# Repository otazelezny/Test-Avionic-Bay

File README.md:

# Test-Avionic-Bay
Avionic bay for testing purposes.

just an general idea how it should looks

v2 (7/31/2024)

schematic v1

schematic partly routed

V1.2 - To improve
    -   Better routing 
    -   coil - XFL4020-152ML                    DONE
    -   more troughput trough routes
    -   probe pins 
    -   more outputs and systematic desing
    -   40x40 hole pattern
    -   more cabel holes
    -   big ground plane to sheelding
    -   external 5v input for easier control
    -   continuity charge sense
    -   4 pyro channels                         DONE
    -   second IC for redandency
    -   micro-sd
    -   Thermistor 100k
    -   Neopixel output

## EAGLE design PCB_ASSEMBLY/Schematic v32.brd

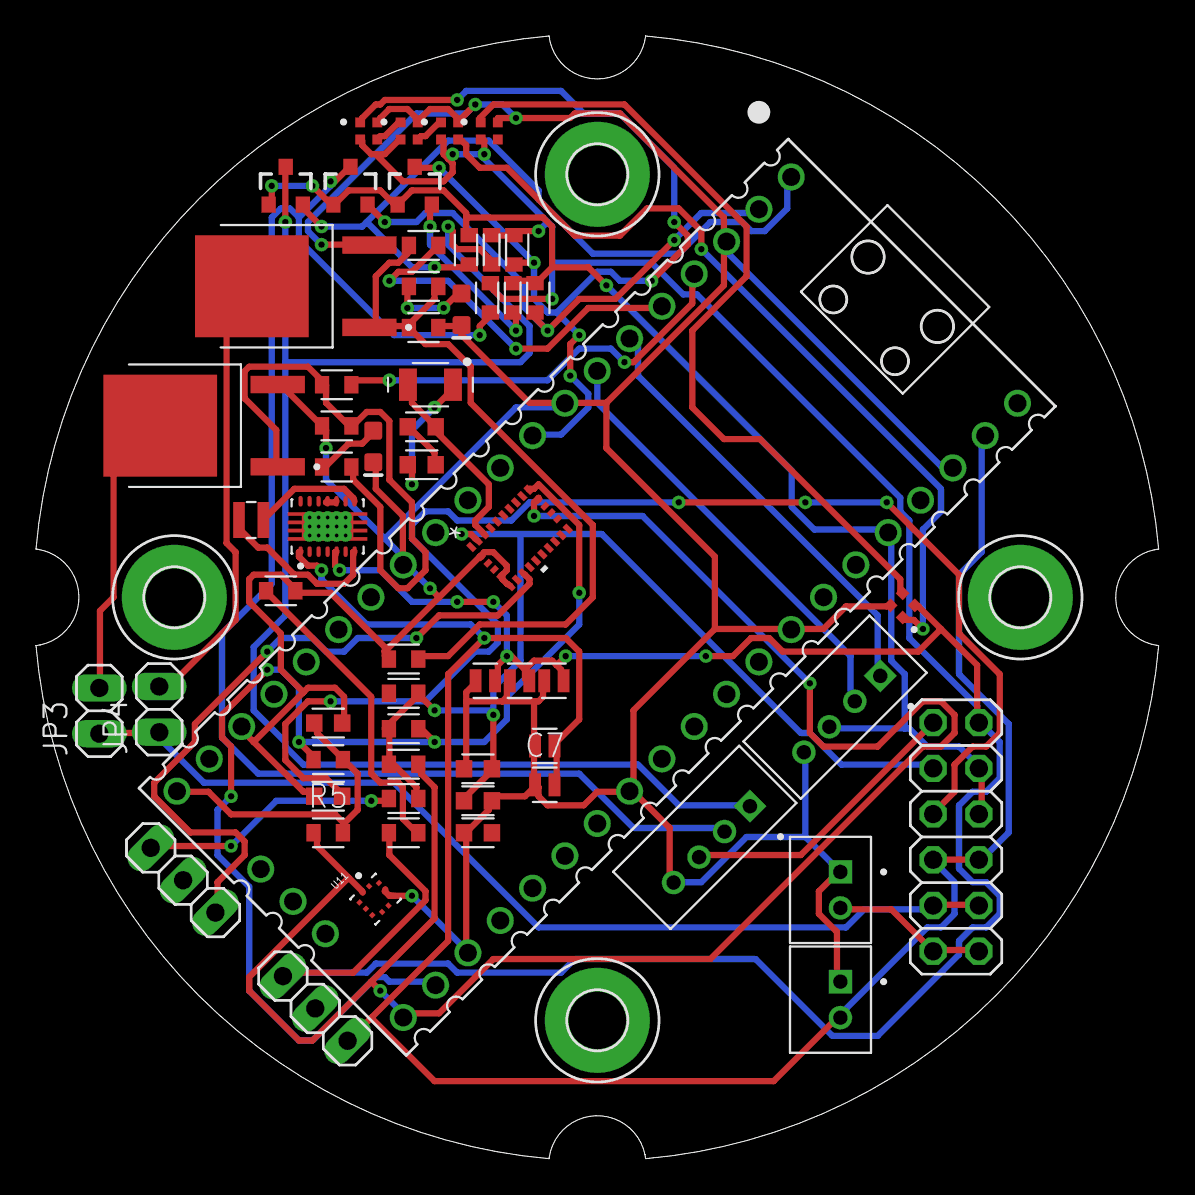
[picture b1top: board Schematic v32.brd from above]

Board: 4 copper layers, 62.2 x 62.2 mm, 64 parts (0 on the bottom side), 45 nets.

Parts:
C1: 1μF; CAPC1608X85
C2, C4, C5: 100nF; CAPC1608X85
C3, C11, C12: 120nF; CAPC1608X85
C6: 10n; CAPC1110X102
C7: 100n; CAPC1110X102
C8, C10: 22UF; CAPC1110X102
C9: 22uF; CAPC1110X102
D1, D2: Red; LED-0603
H1, H2, H3, H4: MOUNT-PAD-ROUND3.2; 3,2-PAD
J1, J2: B4B-PH-KL(LF)(SN); JST_B4B-PH-KL(LF)(SN)
J3, J4: B2B-PH-K-S(LF)(SN); JST_B2B-PH-K-S(LF)(SN)
JP1, JP2: PINHD-1X3; 1X03
JP3, JP4: PINHD-1X2; 1X02
JP5: PINHD-2X6; 2X06
L1: 1.5uH; INDUCTOR_2X2
Q1, Q2, Q3: 220mA/50V/3.5Ω; SOT23-3
Q4, Q5: AOD4184A; DPAK228P994X240-4N
R1, R4, R7, R8, R9, R10, R11, R12: 10K; RESC1608X60
R2, R3, R5, R6: 4.7K; RESC1608X60
R13, R14, R15, R16, R17, R18, R19, R20, R21: RESC1608X60
U1: BNO055QFN_BNO055_BOS; QFN_BNO055_BOS
U2: RASPBERRY_PICOTH; PICO-PKG-TH
U3, U4, U5, U6, U7: 4492; LED_4492
U8: TPS63020DSJR; IC_TPS63020DSJR
U11: BMP390L; XDCR_BMP390L
XTAL1: 32.768 kHz; XTAL330X1051X90N

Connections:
BMP390_INT: U2.10, U11.7
BMP390_MODE_SEL: C5.1, R5.2, R6.2, U2.20, U11.1, U11.6
GND: C1.1, C2.1, C3.2, C4.2, C5.2, C6.1, C7.1, C8.1, C9.1, C10.1, D1.C, D2.C, J1.4, J2.4, J3.1, J4.1, Q4.3, Q5.3, R13.1, R16.1, R19.1, R21.2, U1.2, U1.5, U1.6, U1.18, U1.25, U2.3, U2.8, U2.13, U2.18, U2.23, U2.28, U2.33, U2.38, U3.4, U4.4, U5.4, U6.4, U7.4, U8.2, U8.15, U11.3, U11.8, U11.9
HV_DATA_NEOPIXEL: Q3.3, R9.1, U2.9, U3.1
HV_RX_ELRS: J2.1, Q2.3, R8.1
HV_TX_ELRS: J2.2, Q1.3, R10.1
LV_DATA_NEOPIXEL: Q3.2, R11.1
LV_RX_ELRS: Q2.2, R7.1, U2.1
LV_TX_ELRS: Q1.2, R12.1, U2.2
unnamed: C1.2, U1.9
unnamed: R1.1, U1.4
unnamed: L1.P$1, U8.8, U8.9
unnamed: U3.3, U4.1
unnamed: U4.3, U5.1
unnamed: U5.3, U6.1
unnamed: U6.3, U7.1
unnamed: L1.P$2, U8.6, U8.7
unnamed: R14.2, R21.1, U8.3
unnamed: JP1.2, U8.13
unnamed: Q4.1, R15.2, R16.2, R17.1
unnamed: D1.A, R15.1
unnamed: JP3.2, Q4.4
unnamed: Q5.1, R13.2, R18.2, R19.2, R20.1
unnamed: D2.A, R18.1
unnamed: JP4.2, Q5.4
unnamed: C12.1, U1.26, XTAL1.1
unnamed: C11.1, U1.27, XTAL1.2
unnamed: C11.2, C12.2
NRESET: JP2.3, R4.1, U1.11
RX_GPS: J1.1, U2.6
SCL: R3.2, R5.1, U1.19, U2.21, U11.2
SDA: R2.2, R6.1, U1.20, U2.22, U11.4
SWCLK_BNO055: JP2.1, U1.8
SWDIO_BNO055: JP2.2, U1.7
TRIG_CHARGE_1: R17.2, U2.4
TRIG_CHARGE_2: R20.2, U2.5
TX_GPS: J1.2, U2.7
VCC_3_3: J1.3, JP5.4, JP5.6, Q1.1, Q2.1, Q3.1, R7.2, R11.2, R12.2, U2.36
VCC_3_3_BMP390L: C4.1, JP5.5, U11.10
VCC_3_3_BNO055: C2.2, C3.1, JP5.3, R1.2, R2.1, R3.1, R4.2, U1.3, U1.28
VCC_5: C8.2, C9.2, C10.2, JP1.3, JP5.2, R8.2, R9.2, R10.2, R14.1, U3.2, U4.2, U5.2, U6.2, U7.2, U8.4, U8.5
VCC_5_ELRS: J2.3, JP5.1
VCC_CHARGES: JP3.1, JP4.1, JP5.9, JP5.10
VCC_IN: C6.2, C7.2, J3.2, JP1.1, JP5.7, JP5.8, U2.39, U8.1, U8.10, U8.11, U8.12
VCC_IN_CHARGES: J4.2, JP5.11, JP5.12

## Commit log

2024-08-13 pcb lib update
2024-08-13 new ELRS pcb lib
2024-08-14 another version of pcb schema
2024-08-14 new version
2024-08-16 huge update of the pcb
2024-08-18 Dirextory, new models
2024-09-13 V1.2 started
2024-10-03 readme update

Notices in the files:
parts and their libraries:
SparkFun-DiscreteSemi: Licensing: Creative Commons ShareAlike 4.0 International - https://creativecommons.org/licenses/by-sa/4.0
COPYRIGHT: Copyright (C) 2024 Ultra Librarian. All rights reserved.
